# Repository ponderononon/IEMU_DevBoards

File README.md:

# IEMU Development Boards - Open-source Inertial Sensor for Biomechanics

Kicad Schematic Files for the BASE and SENSOR Development Boards
(Layout in Progress)

The Sensor is a 320g IMU with a magnetometer and NAND-Flash running on a nrf54l15-Module.
The Base works as the coordinator and charger for multiple sensors also utilizing the same Module.

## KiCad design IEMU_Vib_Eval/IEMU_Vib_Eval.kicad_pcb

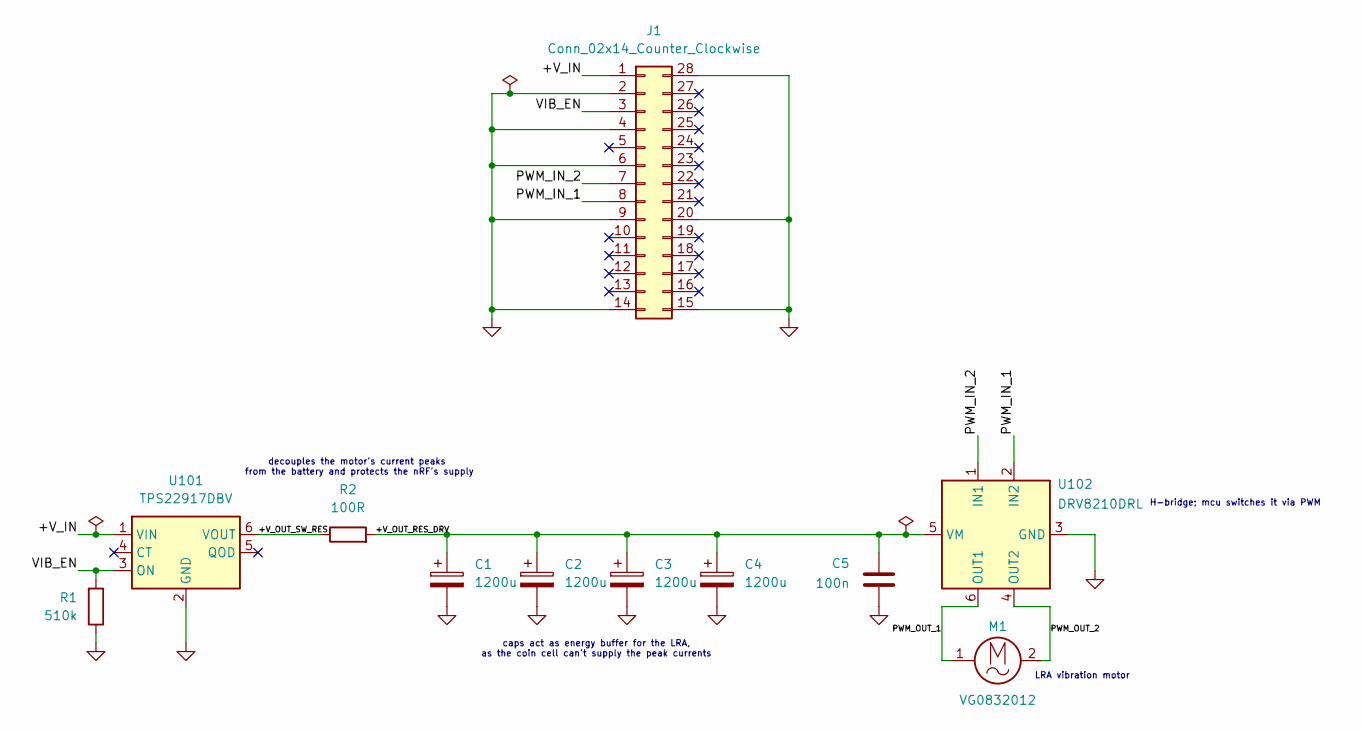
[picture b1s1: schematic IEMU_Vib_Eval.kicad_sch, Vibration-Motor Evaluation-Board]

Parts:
C1, C2, C3, C4: 1200u; C_Radial_D8.0mm_H11.5mm_P3.50mm; Manufacturer_Part_Number A750KS128M0JAAE014
C5: 100n; C_0402_1005Metric; Manufacturer_Part_Number CL05B104KO5NNNC
J1: Conn_02x14_Counter_Clockwise; PinHeader_2x14_P2.54mm_22mm; Manufacturer_Part_Number MC34735
M1: VG0832012; Manufacturer_Part_Number VG0832012
R1: 510k; R_0603_1608Metric; Manufacturer_Part_Number RC0603FR-07510KL
R2: 100R; R_0805_2012Metric; Manufacturer_Part_Number RCA0805100RFKEA
U101: TPS22917DBV; SOT-23-6; Manufacturer_Part_Number TPS22917DBV
U102: DRV8210DRL; SOT-563; Manufacturer_Part_Number DRV8210DRL

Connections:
/+V_IN: J1.1, U101.1 (VIN)
/+V_OUT_RES_DRV: C1.1, C2.1, C3.1, C4.1, C5.1, R2.2, U102.5 (VM)
/+V_OUT_SW_RES: R2.1, U101.6 (VOUT)
/PWM_IN_1: J1.8, U102.2 (IN2)
/PWM_IN_2: J1.7, U102.1 (IN1)
/PWM_OUT_1: M1.1, U102.6 (OUT1)
/PWM_OUT_2: M1.2, U102.4 (OUT2)
/VIB_EN: J1.3, R1.1, U101.3 (ON)
GND: C1.2, C2.2, C3.2, C4.2, C5.2, J1.2, J1.4, J1.6, J1.9, J1.14, J1.15, J1.20, J1.28, R1.2, U101.2 (GND), U102.3 (GND)

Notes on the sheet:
H-bridge; mcu switches it via PWM
LRA vibration motor
decouples the motor's current peaks from the battery and protects the nRF's supply
caps act as energy buffer for the LRA, as the coin cell can't supply the peak currents

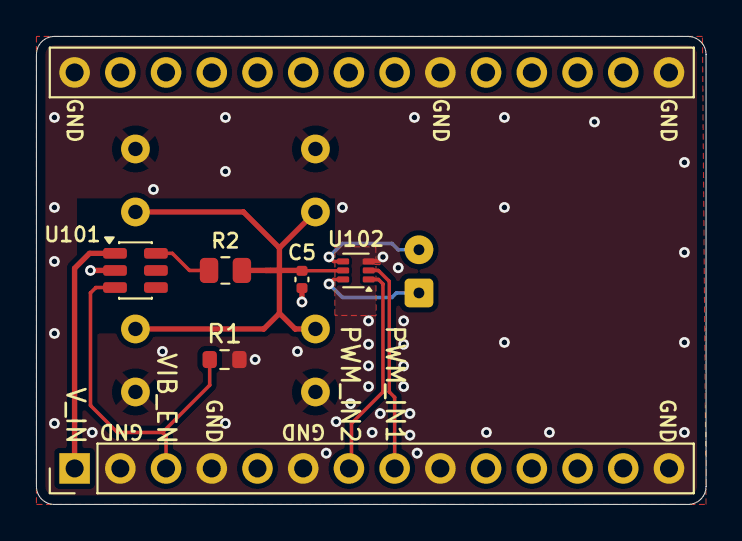
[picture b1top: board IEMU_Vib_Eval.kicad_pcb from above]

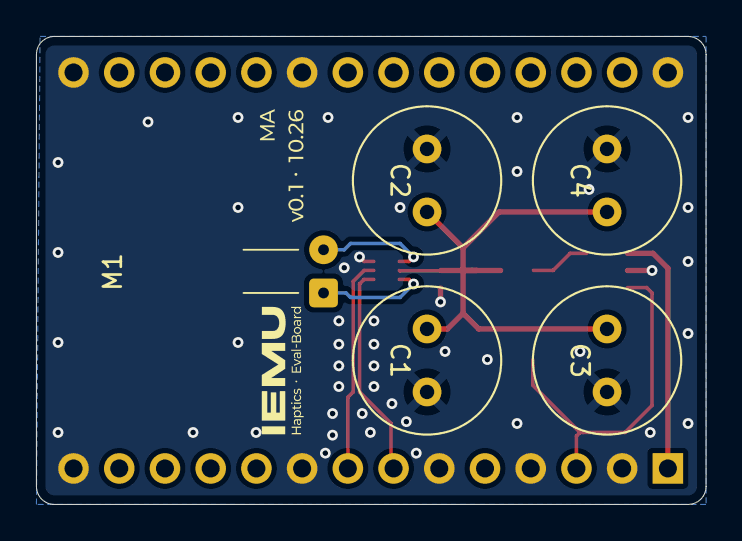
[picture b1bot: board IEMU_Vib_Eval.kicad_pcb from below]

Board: 4 copper layers, 37.2 x 26.0 mm, 11 parts (5 on the bottom side), 9 nets.

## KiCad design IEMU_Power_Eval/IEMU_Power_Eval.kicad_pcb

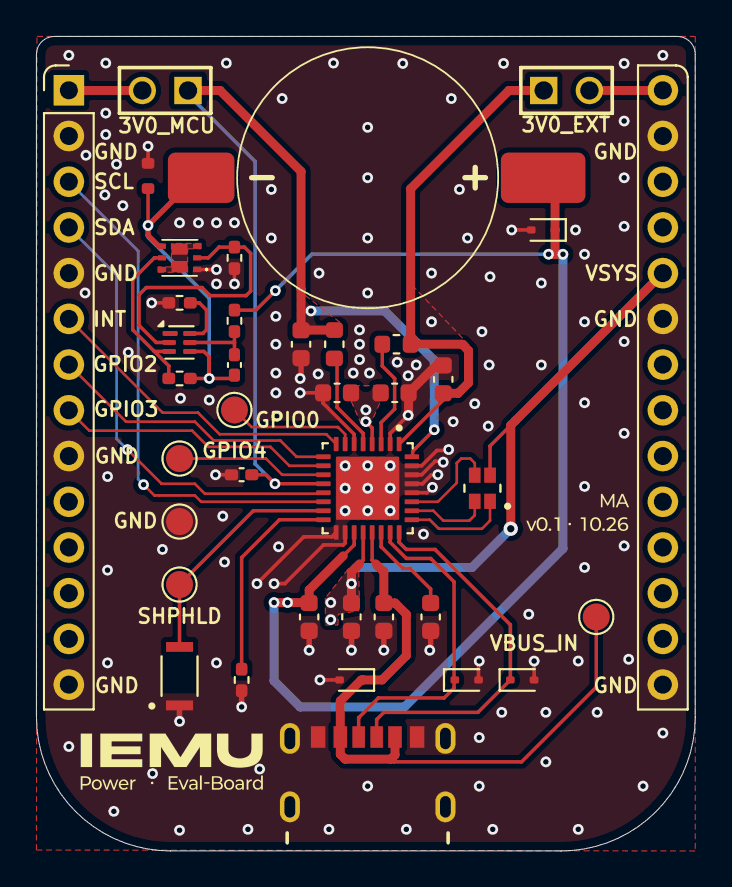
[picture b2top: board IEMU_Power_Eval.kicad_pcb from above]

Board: 4 copper layers, 36.6 x 45.2 mm, 37 parts (0 on the bottom side), 31 nets.

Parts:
BT1: Battery_Cell; CoinCell_LIR1455_LBY2
C1, C2: 1u; C_0603_1608Metric
C3, C4, C5, C9, C10: 10u; C_0603_1608Metric
C6: 2u2; C_0603_1608Metric
C7, C8: 100n; C_0402_1005Metric_Pad0.74x0.62mm_HandSolder
D1, D2, D3, D4: ESD5Z5.0T1G; D_SOD-523_1
D5: TPD1E10B06DYAR; D_SOD-523
D6: LTST-C19HE1WT; LED_LTST-C19HE1WT
GND: TestPoint_Pad_D1.5mm
GPIO0, GPIO4: TestPoint_Pad_D1.5mm
J1: USB4125-GF-A; GCT_USB4125-GF-A_REVA2
J2, J3: Conn_01x02; SAMTEC_MTSW-101-X-X-D-X
J4: Conn_02x14_Counter_Clockwise; PinHeader_2x14_P2.54mm_33mm
L1, L2: 2u2; L_0603_1608Metric
Q1: CSD85301Q2
R1: 150k; R_0402_1005Metric_Pad0.72x0.64mm_HandSolder
R2: 330R; R_0402_1005Metric_Pad0.72x0.64mm_HandSolder
R3, R4: 5M1; R_0402_1005Metric_Pad0.72x0.64mm_HandSolder
R5: 2k2; R_0402_1005Metric_Pad0.72x0.64mm_HandSolder
SHPHLD: TestPoint_Pad_D1.5mm
SW1: SW_Push; SW_EVP-AWED4A
U1: NPM1304-QEAA-R7; QFN50P500X500X90-33N
U2: BQ29702DSER; WSON-6_1.5x1.5mm_P0.5mm
VBUS_IN: TestPoint_Pad_D1.5mm

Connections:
+3V0_EXT: J2.02, J4.28
+3V0_MCU: J3.02, J4.1
+VBAT: BT1.1 (+), C6.1, D4.1 (I/O), R2.1, U1.19 (VBAT)
+VBUS_IN: C1.1, D1.1 (I/O), J1.A9 (VBUS), J1.B9 (VBUS), U1.21 (VBUS), VBUS_IN.1
+VSYS: C3.1, C4.1, C5.1, D6.4, J4.24, U1.4 (PVDD), U1.20 (VSYS)
/+VBUS_OUT: C2.1, U1.22 (VBUSOUT)
/BAT-: BT1.2 (-), C7.2, D5.1 (I/O), Q1.4 (S2), R3.2, U2.4 (VSS)
/BAT_FET: Q1.3 (D2_1), Q1.6 (D1_1), Q1.7 (D1_2), Q1.8 (D2_2)
/BAT_P_BAT: C7.1, R2.2, U2.5 (BAT)
/BAT_P_COUT: Q1.2 (G1), R4.1, U2.2 (COUT)
/BAT_P_DOUT: Q1.5 (G2), R3.1, U2.3 (DOUT)
/BAT_P_V-: R5.1, U2.6 (V-)
/CC1: D2.1 (I/O), J1.A5 (CC1), U1.23 (CC1)
/CC2: D3.1 (I/O), J1.B5 (CC2), U1.24 (CC2)
/GPIO0: GPIO0.1, U1.7 (GPIO0)
/GPIO4: GPIO4.1, U1.11 (GPIO4)
/NPM_LED0: D6.1, U1.25 (LED0)
/NPM_LED1: D6.2, U1.26 (LED1)
/NPM_LED2: D6.3, U1.27 (LED2)
/NPM_SCL: J4.3, U1.14 (SCL)
/NPM_SDA: J4.4, U1.13 (SDA)
/NPM_SW1: L1.2, U1.3 (SW1)
/NPM_SW2: L2.2, U1.5 (SW2)
/NPM_VOUT1: C9.1, J2.01, L1.1, U1.1 (VOUT1)
/NPM_VOUT2: C8.1, C10.1, J3.01, L2.1, U1.12 (VDDIO), U1.32 (VOUT2)
/NPM_VSET2: R1.1, U1.16 (VSET2)
/PMIC_GPIO2: J4.7, U1.9 (GPIO2)
/PMIC_GPIO3: J4.8, U1.10 (GPIO3)
/PMIC_INT: J4.6, U1.8 (GPIO1)
/SHPHLD: SHPHLD.1, SW1.2, U1.15 (SHPHLD)
GND: C1.2, C2.2, C3.2, C4.2, C5.2, C6.2, C8.2, C9.2, C10.2, D1.2 (GND), D2.2 (GND), D3.2 (GND), D4.2 (GND), D5.2 (GND), GND.1, J1.A12 (GND), J1.B12 (GND), J1.S1 (SHIELD), J1.S2 (SHIELD), J1.S3 (SHIELD), J1.S4 (SHIELD), J4.2, J4.5, J4.9, J4.14, J4.15, J4.23, J4.27, Q1.1 (S1), R1.2, R4.2, R5.2, SW1.1, U1.2 (PVSS1), U1.6 (PVSS2), U1.17 (VSET1), U1.18 (NTC), U1.28 (LSIN1/VINLDO1), U1.29 (LSOUT1/VOUTLDO1), U1.30 (LSIN2/VINLDO2), U1.31 (LSOUT2/VOUTLDO2), U1.33 (AVSS)

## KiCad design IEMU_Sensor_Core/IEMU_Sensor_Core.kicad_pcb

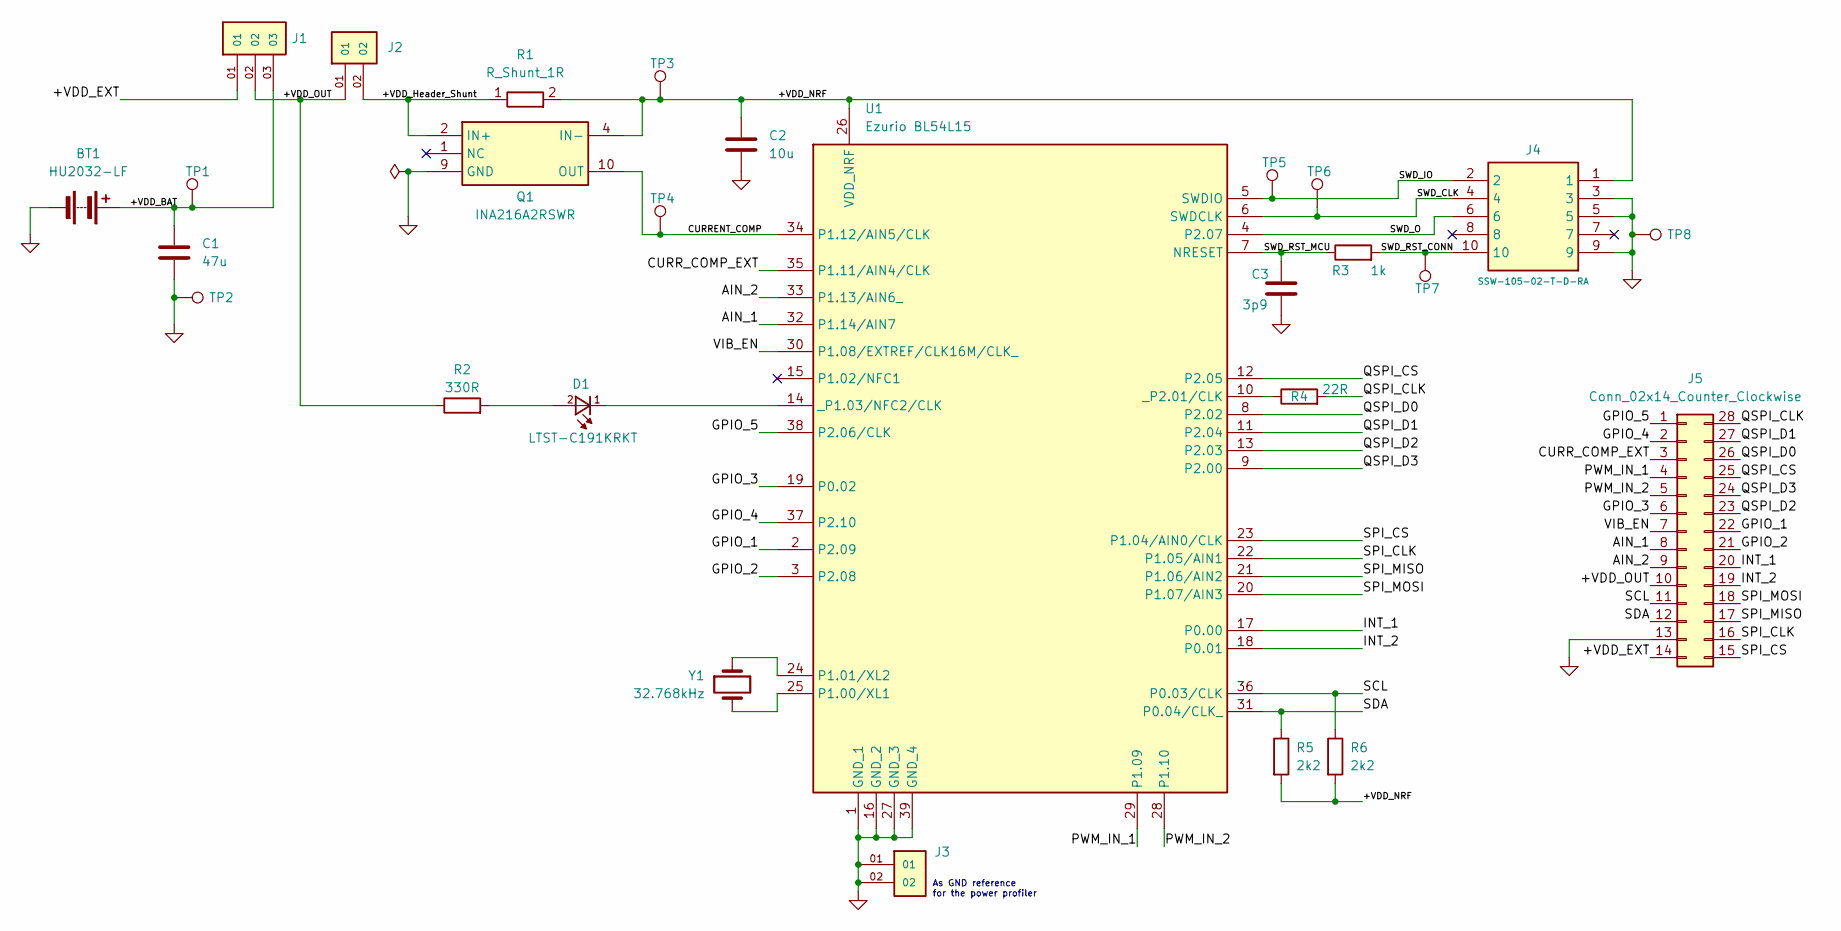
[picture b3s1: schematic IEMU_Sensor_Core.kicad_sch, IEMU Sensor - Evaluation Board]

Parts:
BT1: HU2032-LF; HU2032LF; Manufacturer_Part_Number HU2032-LF
C1: 47u; C_0603_1608Metric; Manufacturer_Part_Number GRM188R60G476ME01D
C2: 10u; C_0603_1608Metric; Manufacturer_Part_Number CL10A106MA8NRNC
C3: 3p9; C_0402_1005Metric_Pad0.74x0.62mm_HandSolder; Manufacturer_Part_Number GCM1555C1H3R9BA16D
D1: LTST-C191KRKT; Manufacturer_Part_Number LTST-C191KRKT; LCSC C125099
J1: MTSW-103-07-T-S-240; SAMTEC_MTSW-103-07-T-S-240; Manufacturer_Part_Number MTSW-103-07-T-S-240
J2, J3: MTSW-101-07-T-D-240; SAMTEC_MTSW-101-X-X-D-X; Manufacturer_Part_Number MTSW-101-07-T-D-240
J4: SSW-105-02-T-D-RA; PinHeader_2x05_P1.27mm_Vertical_SWD_Debug; Manufacturer_Part_Number FTSH-105-01-F-D-K
J5: Conn_02x14_Counter_Clockwise; PinHeader_2x14_P2.54mm_33mm; Manufacturer_Part_Number MC34735
Q1: INA216A2RSWR; Texas_RSW0010A_UQFN-10_1.4x1.8mm_P0.4mm; Manufacturer_Part_Number INA216A2RSWR; LCSC C2653823
R1: R_Shunt_1R; R_0402_1005Metric_Pad0.72x0.64mm_HandSolder; Manufacturer_Part_Number RLP73K1E1R0FTDF; LCSC C2074826
R2: 330R; R_0402_1005Metric_Pad0.72x0.64mm_HandSolder; Manufacturer_Part_Number RC0402FR-07330RL
R3: 1k; R_0402_1005Metric_Pad0.72x0.64mm_HandSolder; Manufacturer_Part_Number RC0402FR-071KL
R4: 22R; R_0603_1608Metric; Manufacturer_Part_Number RC0603FR-0722RL
R5, R6: 2k2; R_0402_1005Metric_Pad0.72x0.64mm_HandSolder; Manufacturer_Part_Number RC0402FR-072K21L
TP1, TP2, TP3, TP4, TP5, TP6, TP7, TP8: TestPoint; TestPoint_Pad_D1.5mm
U1: Ezurio BL54L15; BL54L15; Manufacturer_Part_Number 453-00001C
Y1: 32.768kHz; Crystal_SMD_3215-2Pin_3.2x1.5mm; Manufacturer_Part_Number SC-32S32.768kHz20PPM9pF; LCSC C97605

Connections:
/+VDD_BAT: BT1.1 (+), BT1.2 (+), C1.1, J1.03, TP1.1
/+VDD_EXT: J1.01, J5.14
/+VDD_Header_Shunt: J2.02, Q1.2 (IN+), Q1.3 (IN+), R1.1
/+VDD_NRF: C2.1, J4.1, Q1.4 (IN-), Q1.5 (IN-), R1.2, R5.2, R6.2, TP3.1, U1.26 (VDD_NRF)
/+VDD_OUT: J1.02, J2.01, J5.10, R2.1
/AIN_1: J5.8, U1.32 (P1.14/AIN7)
/AIN_2: J5.9, U1.33 (P1.13/AIN6_)
/CURRENT_COMP: Q1.10 (OUT), TP4.1, U1.34 (P1.12/AIN5/CLK)
/CURR_COMP_EXT: J5.3, U1.35 (P1.11/AIN4/CLK)
/GPIO_1: J5.22, U1.2 (P2.09)
/GPIO_2: J5.21, U1.3 (P2.08)
/GPIO_3: J5.6, U1.19 (P0.02)
/GPIO_4: J5.2, U1.37 (P2.10)
/GPIO_5: J5.1, U1.38 (P2.06/CLK)
/INT_1: J5.20, U1.17 (P0.00)
/INT_2: J5.19, U1.18 (P0.01)
/PWM_IN_1: J5.4, U1.29 (P1.09)
/PWM_IN_2: J5.5, U1.28 (P1.10)
/QSPI_CLK: J5.28, R4.2
/QSPI_CS: J5.25, U1.12 (P2.05)
/QSPI_D0: J5.26, U1.8 (P2.02)
/QSPI_D1: J5.27, U1.11 (P2.04)
/QSPI_D2: J5.23, U1.13 (P2.03)
/QSPI_D3: J5.24, U1.9 (P2.00)
/SCL: J5.11, R6.1, U1.36 (P0.03/CLK)
/SDA: J5.12, R5.1, U1.31 (P0.04/CLK_)
/SPI_CLK: J5.16, U1.22 (P1.05/AIN1)
/SPI_CS: J5.15, U1.23 (P1.04/AIN0/CLK)
/SPI_MISO: J5.17, U1.21 (P1.06/AIN2)
/SPI_MOSI: J5.18, U1.20 (P1.07/AIN3)
/SWD_CLK: J4.4, TP6.1, U1.6 (SWDCLK)
/SWD_IO: J4.2, TP5.1, U1.5 (SWDIO)
/SWD_O: J4.6, U1.4 (P2.07)
/SWD_RST_CONN: J4.10, R3.2, TP7.1
/SWD_RST_MCU: C3.1, R3.1, U1.7 (NRESET)
/VIB_EN: J5.7, U1.30 (P1.08/EXTREF/CLK16M/CLK_)
GND: BT1.3 (-), C1.2, C2.2, C3.2, J3.01, J3.02, J4.3, J4.5, J4.9, J5.13, Q1.9 (GND), TP2.1, TP8.1, U1.1 (GND_1), U1.16 (GND_2), U1.27 (GND_3), U1.39 (GND_4)
unnamed: D1.2, R2.2
unnamed: U1.25 (P1.00/XL1), Y1.2
unnamed: U1.24 (P1.01/XL2), Y1.1
unnamed: D1.1, U1.14 (_P1.03/NFC2/CLK)
unnamed: R4.1, U1.10 (_P2.01/CLK)

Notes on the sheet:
As GND reference for the power profiler

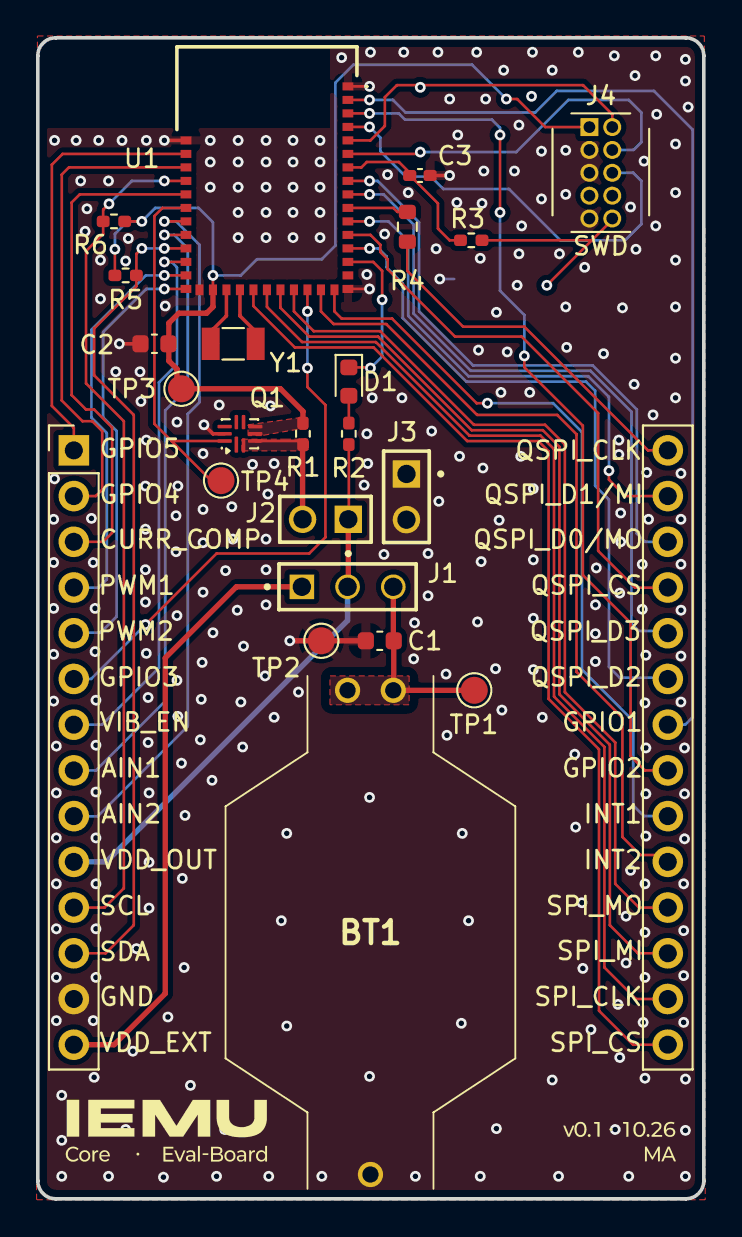
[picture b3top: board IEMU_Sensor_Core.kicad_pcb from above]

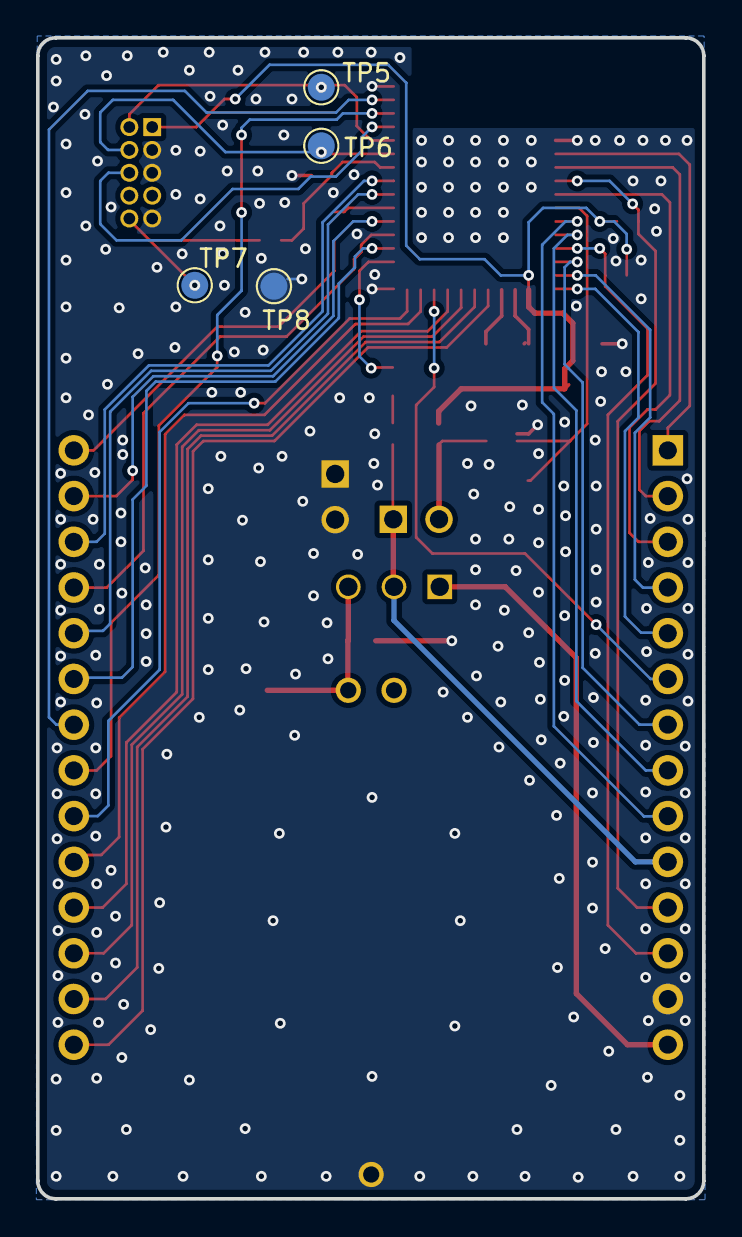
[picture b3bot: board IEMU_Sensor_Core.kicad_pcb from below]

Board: 4 copper layers, 37.0 x 64.5 mm, 27 parts (4 on the bottom side), 42 nets.

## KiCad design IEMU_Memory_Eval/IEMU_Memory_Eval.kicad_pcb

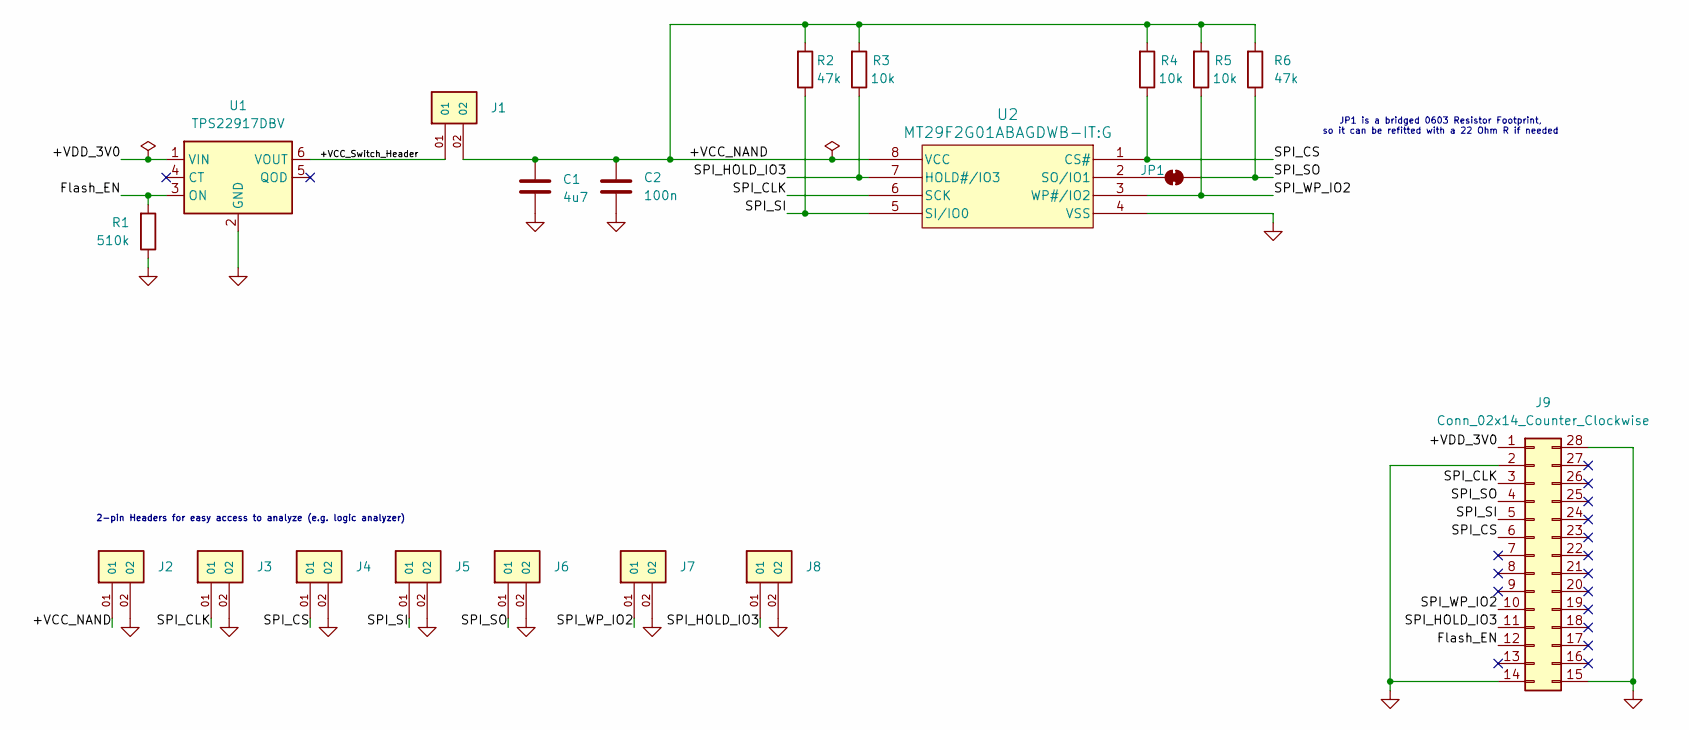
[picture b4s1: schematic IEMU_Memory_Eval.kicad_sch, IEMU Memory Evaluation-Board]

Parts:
C1: 4u7; R_0402_1005Metric_Pad0.72x0.64mm_HandSolder; Manufacturer_Part_Number C1005X5R1A475K050BC
C2: 100n; R_0402_1005Metric_Pad0.72x0.64mm_HandSolder; Manufacturer_Part_Number CL05B104KO5NNNC; LCSC C1525
J1, J2, J3, J4, J5, J6, J7, J8: 2211S-02G; SAMTEC_MTSW-101-X-X-D-X; Manufacturer_Part_Number 2211S-02G
J9: Conn_02x14_Counter_Clockwise; PinHeader_2x14_P2.54mm_26mm
JP1: SolderJumper_2_Bridged; R_bridged_0603_1608Metric_Pad0.98x0.95mm_HandSolder
R1: 510k; R_0603_1608Metric; Manufacturer_Part_Number RC0603FR-07510KL
R2, R6: 47k; R_0402_1005Metric_Pad0.72x0.64mm_HandSolder; Manufacturer_Part_Number RC0402FR-0747KL
R3, R4, R5: 10k; R_0402_1005Metric_Pad0.72x0.64mm_HandSolder; Manufacturer_Part_Number RC0402FR-0710KL
U1: TPS22917DBV; SOT-23-6; Manufacturer_Part_Number TPS22917DBV
U2: MT29F2G01ABAGDWB-IT:G; U-PDFN-8_8x6mm; Manufacturer_Part_Number MT29F2G01ABAGDWB-IT:G

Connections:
/+VCC_NAND: C1.1, C2.1, J1.02, J2.01, R2.1, R3.1, R4.1, R5.1, R6.1, U2.8 (VCC)
/+VCC_Switch_Header: J1.01, U1.6 (VOUT)
/+VDD_3V0: J9.1, U1.1 (VIN)
/Flash_EN: J9.12, R1.1, U1.3 (ON)
/SPI_CLK: J3.01, J9.3, U2.6 (SCK)
/SPI_CS: J4.01, J9.6, R4.2, U2.1 (CS#)
/SPI_HOLD_IO3: J8.01, J9.11, R3.2, U2.7 (HOLD#/IO3)
/SPI_SI: J5.01, J9.5, R2.2, U2.5 (SI/IO0)
/SPI_SO: J6.01, J9.4, JP1.2 (B), R6.2
/SPI_WP_IO2: J7.01, J9.10, R5.2, U2.3 (WP#/IO2)
GND: C1.2, C2.2, J2.02, J3.02, J4.02, J5.02, J6.02, J7.02, J8.02, J9.2, J9.14, J9.15, J9.28, R1.2, U1.2 (GND), U2.4 (VSS)
unnamed: JP1.1 (A), U2.2 (SO/IO1)

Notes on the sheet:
JP1 is a bridged 0603 Resistor Footprint, so it can be refitted with a 22 Ohm R if needed
2-pin Headers for easy access to analyze (e.g. logic analyzer)

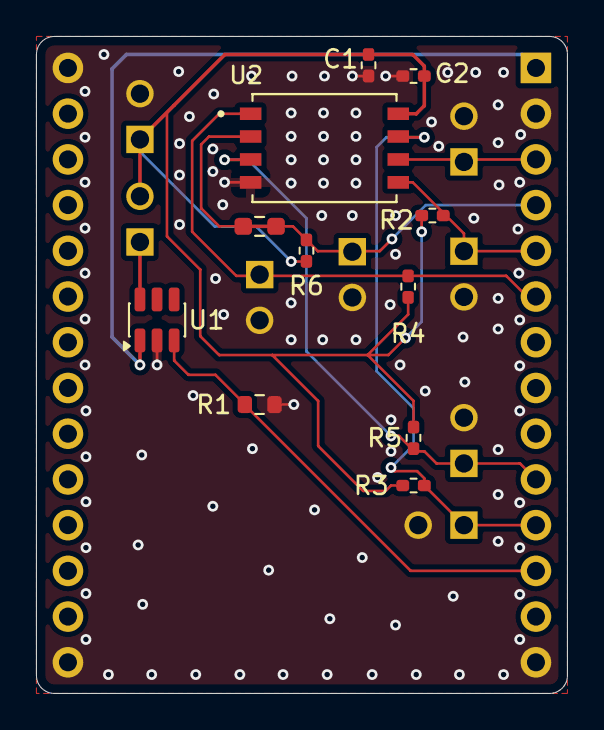
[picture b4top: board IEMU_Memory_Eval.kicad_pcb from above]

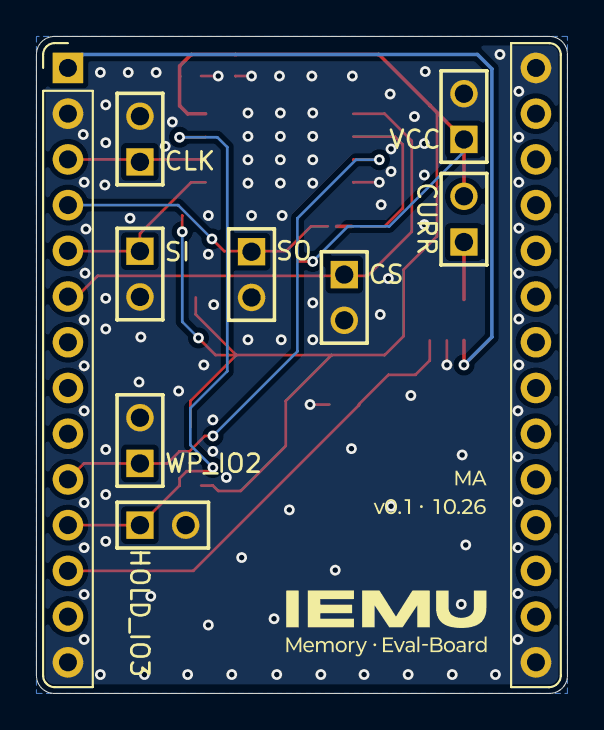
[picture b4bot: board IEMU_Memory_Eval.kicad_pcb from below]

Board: 4 copper layers, 29.5 x 36.5 mm, 20 parts (9 on the bottom side), 12 nets.

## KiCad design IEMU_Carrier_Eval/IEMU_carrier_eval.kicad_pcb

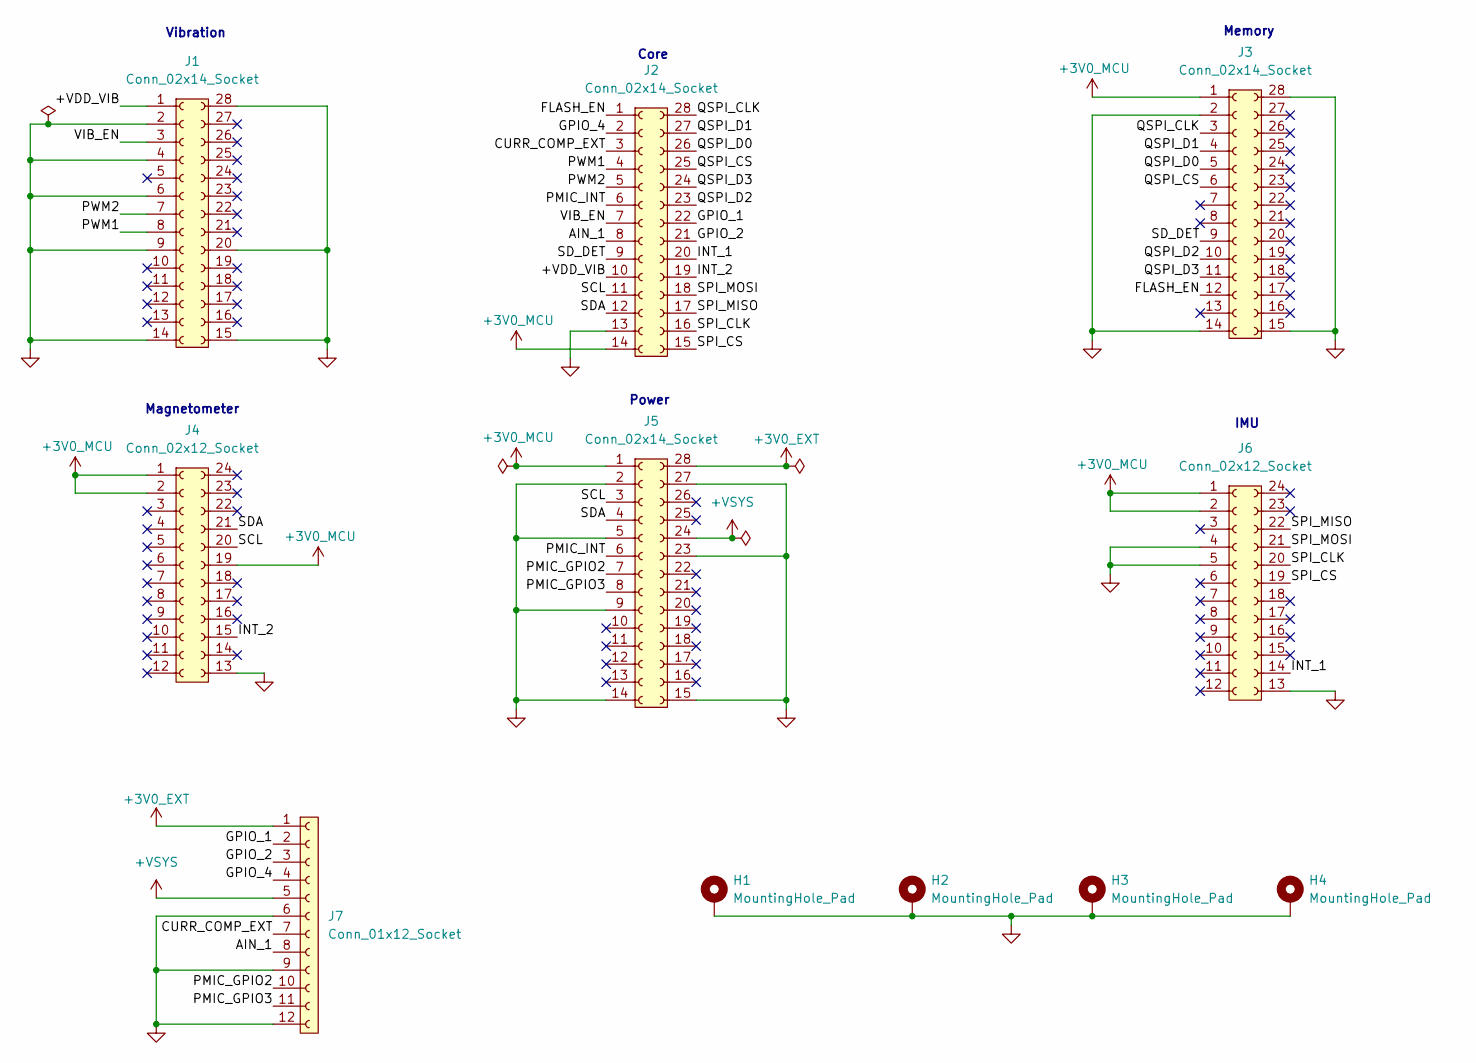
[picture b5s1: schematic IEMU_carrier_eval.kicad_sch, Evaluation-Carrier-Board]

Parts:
H1, H2, H3, H4: MountingHole_Pad; MountingHole_1.2mm_M2_Pad_Via
J1: Conn_02x14_Socket; PinSocket_2x14_P2.54mm_22mm
J2, J5: Conn_02x14_Socket; PinSocket_2x14_P2.54mm_33mm
J3: Conn_02x14_Socket; PinSocket_2x14_P2.54mm_26mm
J4, J6: Conn_02x12_Socket; PinSocket_2x12_P2.54mm_15mm
J7: Conn_01x12_Socket; PinHeader_1x12_P2.54mm_Vertical

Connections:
+3V0_EXT: J5.28 (Pin_14), J7.1
+3V0_MCU: J2.14, J3.1, J4.1, J4.2, J4.19 (18), J5.1, J6.1, J6.2
+VSYS: J5.24 (Pin_10), J7.5
/+VDD_VIB: J1.1, J2.10
/AIN_1: J2.8, J7.8
/CURR_COMP_EXT: J2.3, J7.7
/FLASH_EN: J2.1, J3.12
/GPIO_1: J2.22 (Pin_8), J7.2
/GPIO_2: J2.21 (Pin_7), J7.3
/GPIO_4: J2.2, J7.4
/INT_1: J2.20 (Pin_6), J6.14 (Pin_4)
/INT_2: J2.19 (Pin_5), J4.15 (Pin_5)
/PMIC_GPIO2: J5.7, J7.10
/PMIC_GPIO3: J5.8, J7.11
/PMIC_INT: J2.6, J5.6
/PWM1: J1.8, J2.4
/PWM2: J1.7, J2.5
/QSPI_CLK: J2.28 (Pin_14), J3.3
/QSPI_CS: J2.25 (Pin_11), J3.6
/QSPI_D0: J2.26 (Pin_12), J3.5
/QSPI_D1: J2.27 (Pin_13), J3.4
/QSPI_D2: J2.23 (Pin_9), J3.10
/QSPI_D3: J2.24 (Pin_10), J3.11
/SCL: J2.11, J4.20 (Pin_10), J5.3
/SDA: J2.12, J4.21 (Pin_11), J5.4
/SD_DET: J2.9, J3.9
/SPI_CLK: J2.16 (Pin_2), J6.20 (Pin_10)
/SPI_CS: J2.15 (Pin_1), J6.19 (18)
/SPI_MISO: J2.17 (Pin_3), J6.22 (Pin_12)
/SPI_MOSI: J2.18 (Pin_4), J6.21 (Pin_11)
/VIB_EN: J1.3, J2.7
GND: H1.1, H2.1, H3.1, H4.1, J1.2, J1.4, J1.6, J1.9, J1.14, J1.15 (Pin_1), J1.20 (Pin_6), J1.28 (Pin_14), J2.13, J3.2, J3.14, J3.15 (Pin_1), J3.28 (Pin_14), J4.13 (Pin_3), J5.2, J5.5, J5.9, J5.14, J5.15 (Pin_1), J5.23 (Pin_9), J5.27 (Pin_13), J6.4, J6.5, J6.13 (Pin_3), J7.6, J7.9, J7.12

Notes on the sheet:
Vibration
Memory
Magnetometer
IMU
Core
Power

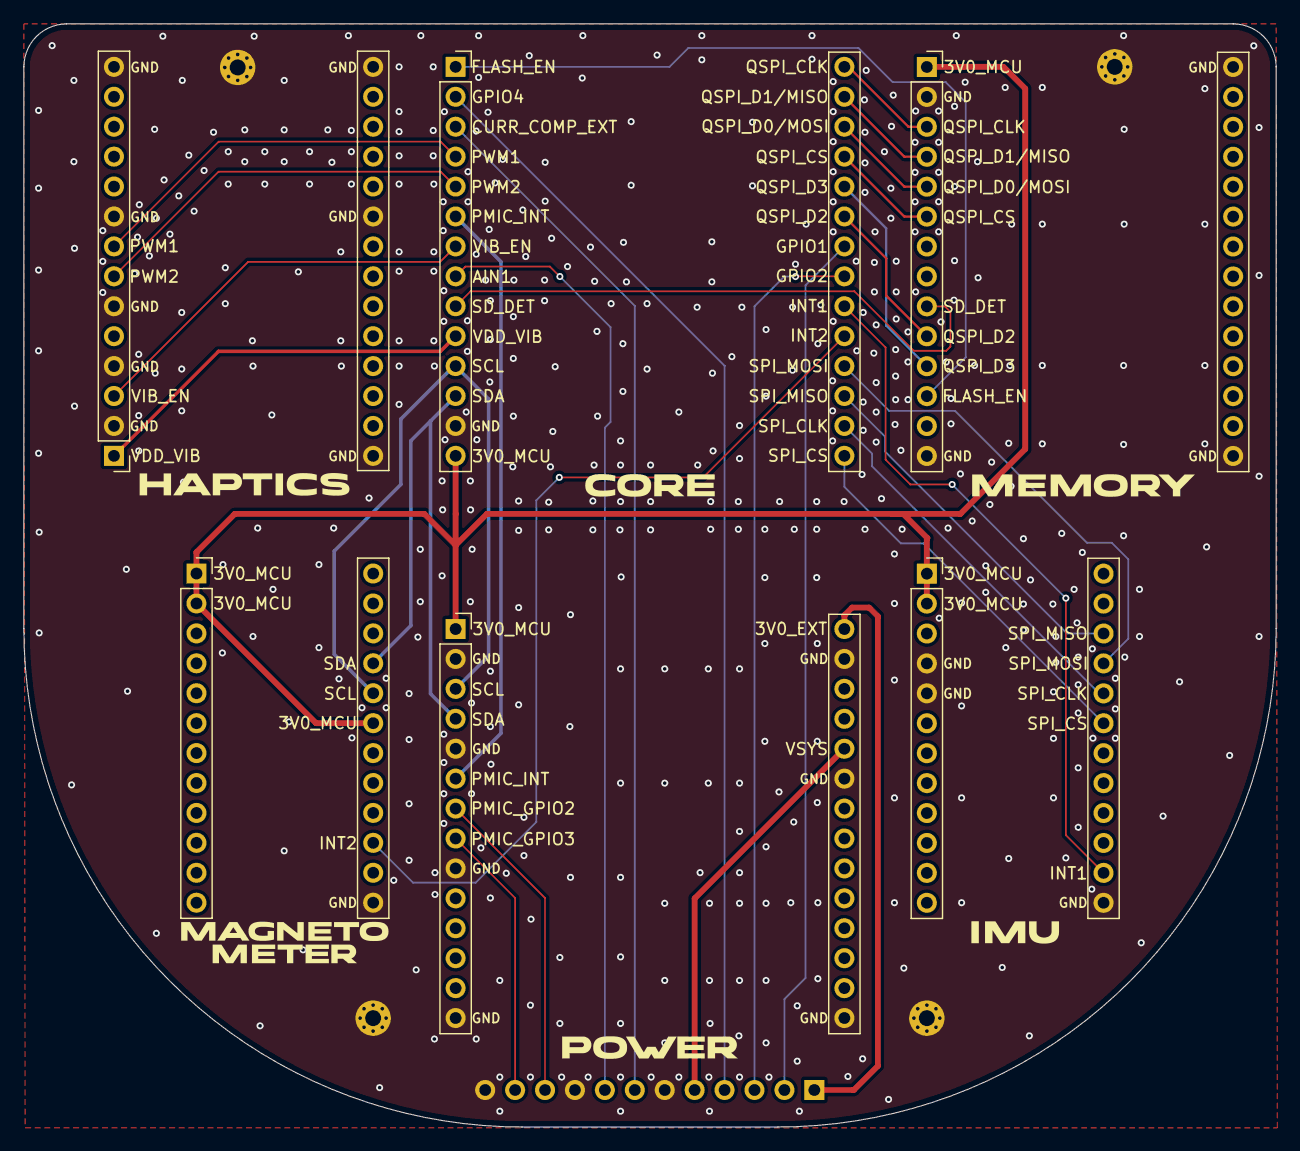
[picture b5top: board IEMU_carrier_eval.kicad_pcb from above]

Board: 4 copper layers, 106.3 x 93.6 mm, 11 parts (1 on the bottom side), 32 nets.

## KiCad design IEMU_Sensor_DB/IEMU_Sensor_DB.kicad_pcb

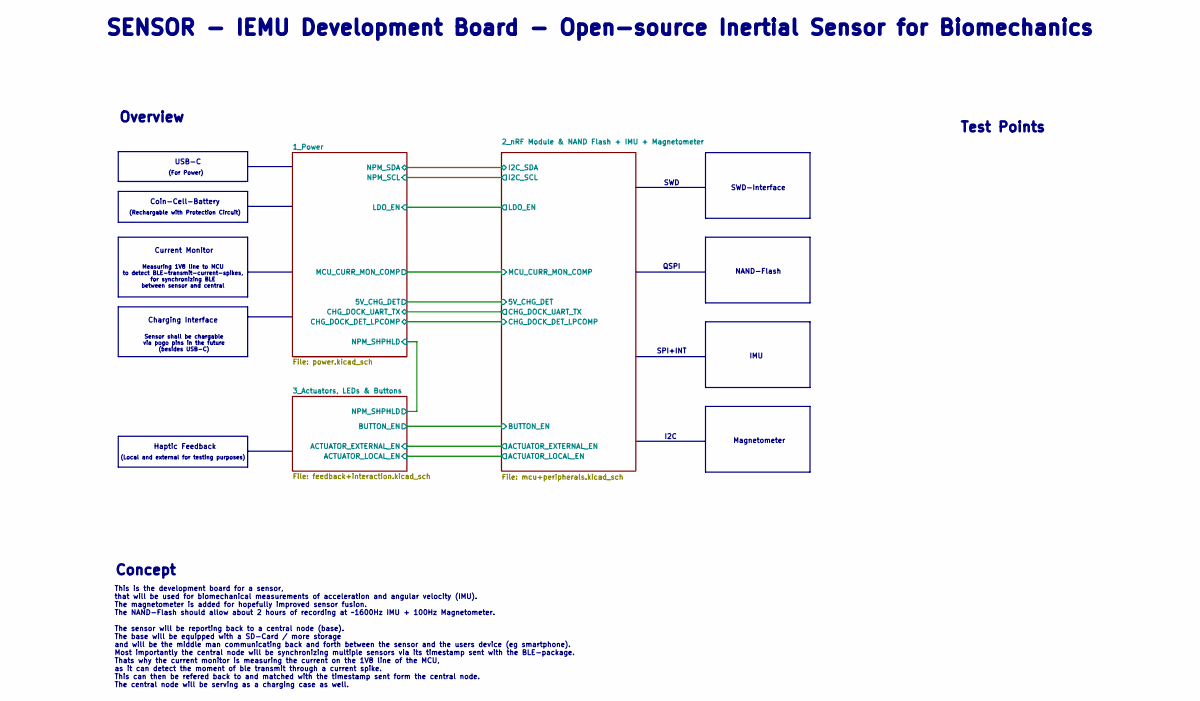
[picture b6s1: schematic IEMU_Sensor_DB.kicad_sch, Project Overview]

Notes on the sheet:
(Rechargable with Protection Circuit)
SWD
Current Monitor
(Local and external for testing purposes)
Concept
USB-C
This is the development board for a sensor, that will be used for biomechanical measurements of acceleration and angular velocity (IMU). The magnetometer is added for hopefully improved sensor fusion. The NAND-Flash should allow about 2 hours of recording at ~1600Hz IMU + 100Hz Magnetometer. The se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
Magnetometer
NAND-Flash
IMU
(For Power)
I2C
Coin-Cell-Battery
Charging Interface
SWD-Interface
Measuring 1V8 line to MCU to detect BLE-transmit-current-spikes, for synchronizing BLE between sensor and central
Test Points
Sensor shall be chargable via pogo pins in the future (besides USB-C)
QSPI
Overview
Haptic Feedback
SPI+INT
SENSOR - IEMU Development Board - Open-source Inertial Sensor for Biomechanics
